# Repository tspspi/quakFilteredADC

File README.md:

# ADC pre-filter (25 kHz) and balun/prescale board

This is the ADC pre-filter and balun/prescaler board for the
QUAK/ESR and QUASEM project to be used between the I/Q demodulation
and the PICO board.

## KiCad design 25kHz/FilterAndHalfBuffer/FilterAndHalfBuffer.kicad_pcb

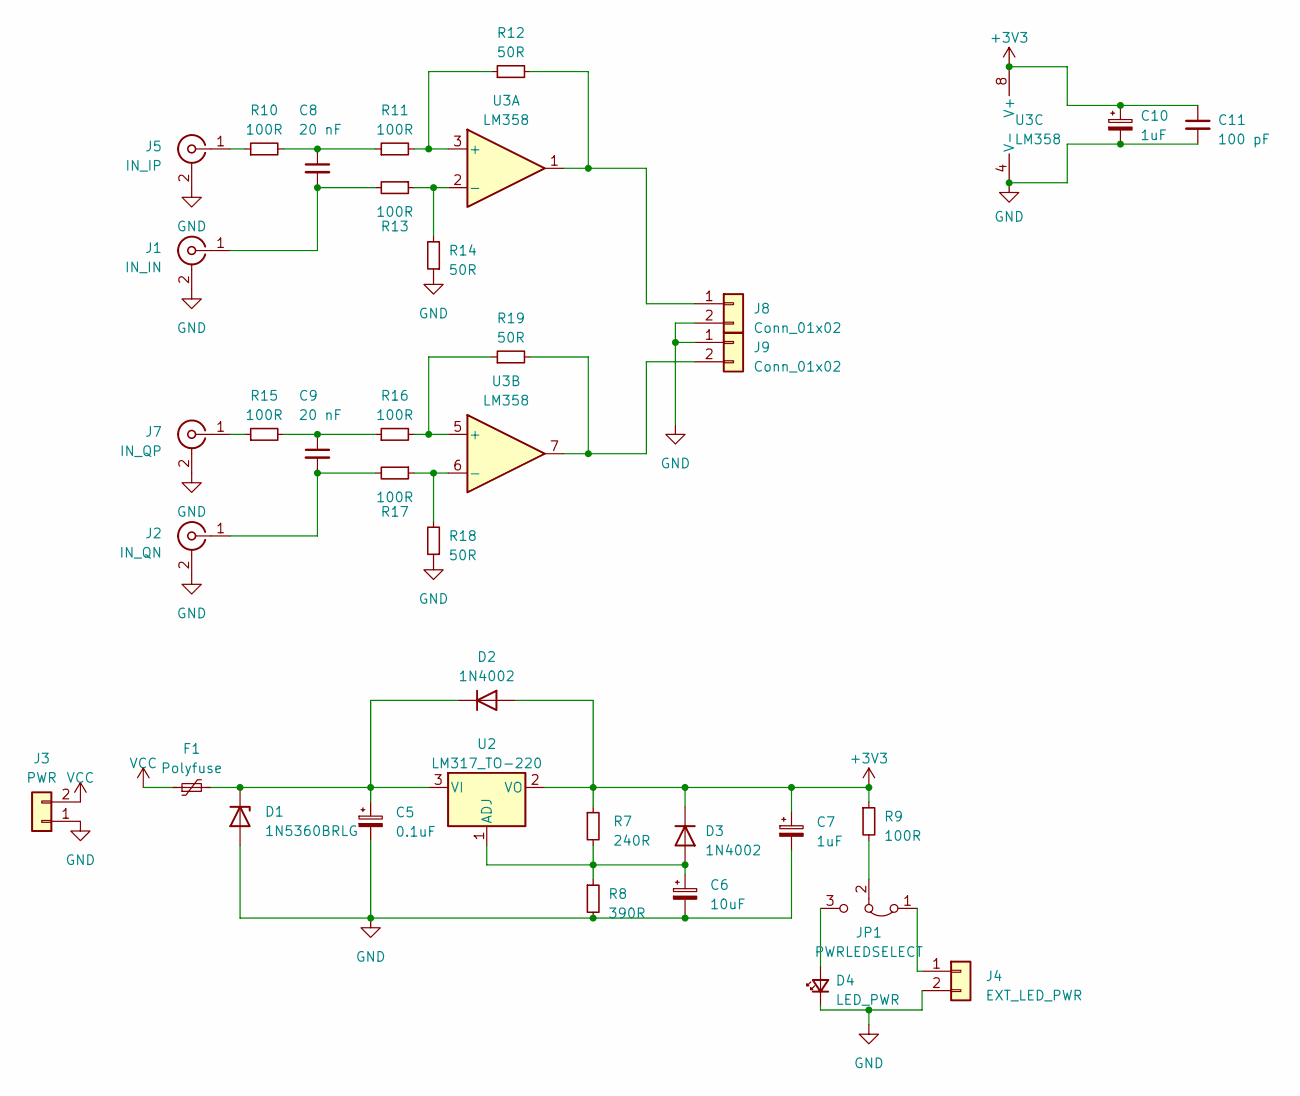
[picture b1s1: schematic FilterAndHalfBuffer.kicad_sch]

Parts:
C5: 0.1uF; C_0805_2012Metric
C6: 10uF; CP_EIA-7343-20_Kemet-V
C7, C10: 1uF; C_0805_2012Metric
C8, C9: 20 nF; C_0805_2012Metric
C11: 100 pF; C_0805_2012Metric
D1: 1N5360BRLG; D_DO-41_SOD81_P12.70mm_Horizontal
D2, D3: 1N4002; D_DO-41_SOD81_P10.16mm_Horizontal
D4: LED_PWR; LED_0805_2012Metric
F1: Polyfuse; C_Disc_D5.1mm_W3.2mm_P5.00mm
J1: IN_IN; SMA_Amphenol_901-143_Horizontal
J2: IN_QN; SMA_Amphenol_901-143_Horizontal
J3: PWR; PinHeader_1x02_P2.54mm_Vertical
J4: EXT_LED_PWR; PinHeader_1x02_P2.54mm_Vertical
J5: IN_IP; SMA_Amphenol_901-143_Horizontal
J7: IN_QP; SMA_Amphenol_901-143_Horizontal
J8, J9: Conn_01x02; PinHeader_1x02_P2.54mm_Vertical
JP1: PWRLEDSELECT; PinHeader_1x03_P2.54mm_Vertical
R7: 240R; R_0805_2012Metric
R8: 390R; R_0805_2012Metric
R9, R10, R11, R13, R15, R16, R17: 100R; R_0805_2012Metric
R12, R14, R18, R19: 50R; R_0805_2012Metric
U2: LM317_TO-220; TO-220-3_Vertical
U3: LM358; SOIC-8_3.9x4.9mm_P1.27mm

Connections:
+3V3: C7.1, C10.1, C11.1, D2.2 (A), D3.1 (K), R7.1, R9.1, U2.2 (VO), U3.8 (V+)
GND: C5.2, C6.2, C7.2, C10.2, C11.2, D1.2 (A), D4.1 (K), J1.2 (Ext), J2.2 (Ext), J3.1, J4.2, J5.2 (Ext), J7.2 (Ext), J8.2, J9.1, R8.2, R14.1, R18.1, U3.4 (V-)
unnamed: C8.1, R10.2, R11.1
unnamed: C9.1, R15.2, R16.1
unnamed: C5.1, D1.1 (K), D2.1 (K), F1.2, U2.3 (VI)
unnamed: C6.1, D3.2 (A), R7.2, R8.1, U2.1 (ADJ)
unnamed: D4.2 (A), JP1.3 (B)
unnamed: C8.2, J1.1 (In), R13.2
unnamed: C9.2, J2.1 (In), R17.2
unnamed: J4.1, JP1.1 (A)
unnamed: J5.1 (In), R10.1
unnamed: J7.1 (In), R15.1
unnamed: J8.1, R12.2, U3.1
unnamed: J9.2, R19.2, U3.7
unnamed: JP1.2 (C), R9.2
unnamed: R11.2, R12.1, U3.3 (+)
unnamed: R13.1, R14.2, U3.2 (-)
unnamed: R16.2, R19.1, U3.5 (+)
unnamed: R17.1, R18.2, U3.6 (-)
VCC: F1.1, J3.2

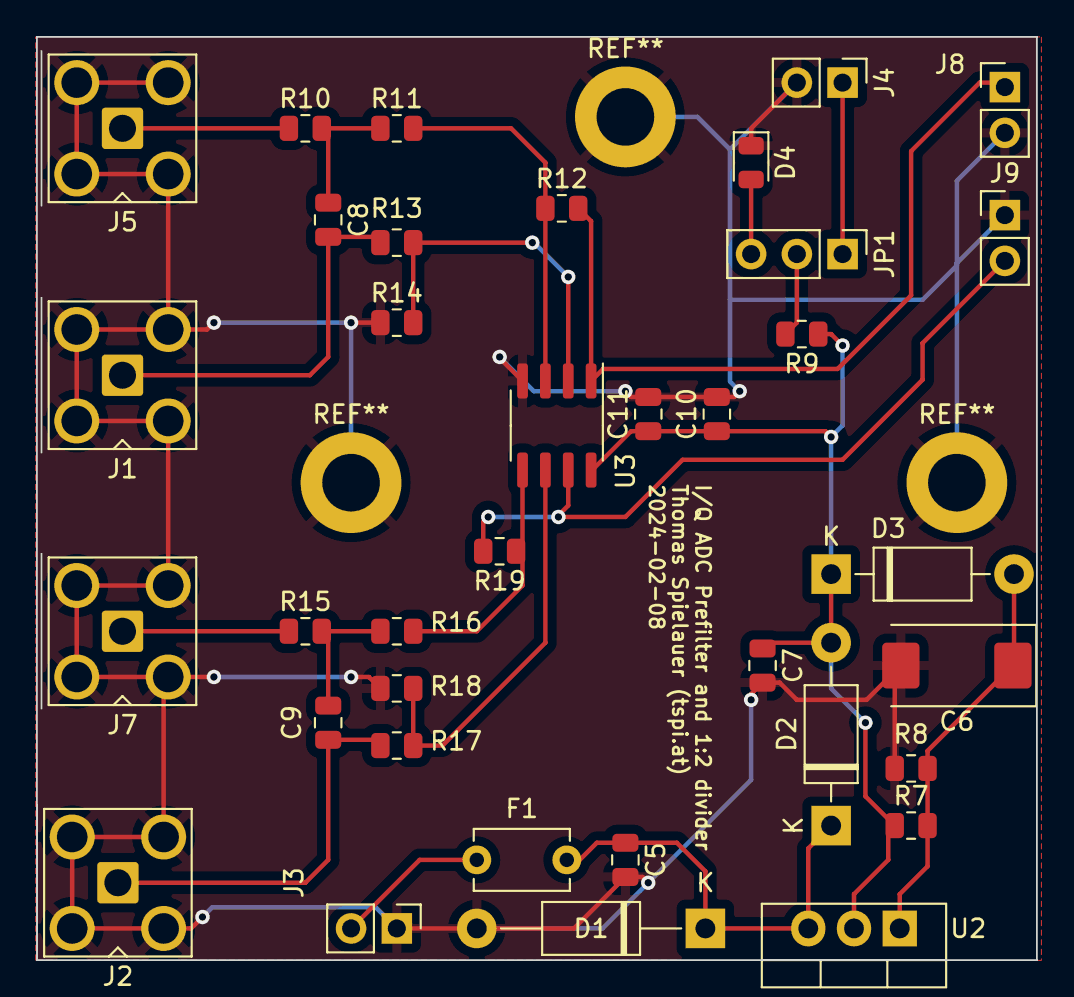
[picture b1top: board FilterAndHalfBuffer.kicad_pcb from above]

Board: 2 copper layers, 55.6 x 51.3 mm, 36 parts (0 on the bottom side), 20 nets.

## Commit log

2024-02-08 Adding board rendering
2024-02-08 Adding rendering reference to README
2024-03-19 Update PCB
